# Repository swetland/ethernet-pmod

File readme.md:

# Ethernet PMOD v2

This PCB is a PMOD (FPGA development board peripheral module) for the
Microchip LAN8720A PHY, to enable 10/100M Ethernet connectivity.

It is configured to accept the necessary 50MHz clock from the FPGA, and
exchanges data using the [RMII standard](https://en.wikipedia.org/wiki/Media-independent_interface#RMII).  A secondary header provides access
to the MDIO/MDC lines to allow access to the management interface.

I have manufactured 10 of these using JLCPCB's PCB fabrication and assembly
service (manually soldering the two throw-hole components myself) and have
used this PMOD successfully with Litex / LiteETH / VexRiscv on a Muse Lab
iCE Sugar Pro FPGA board.

This project is licensed under the [CERN OHL P v2](CERN-OHL-P-v2.txt) Permissive Open Hardware License.

## Design Files and Resources

Original design files are here: [kicad/](kicad/)

Schematic in PDF format here: [export/ethernet-pmod-v2-schematic.pdf](export/ethernet-pmod-v2-schematic.pdf)

Gerbers and CSV files used for a successful JLCPCB order, under [export/jlcpcb/](export/jlcpcb/)

Documentation on the Microchip LAN8720A: https://www.microchip.com/en-us/product/LAN8720A

## Pictures

## PMOD Connector Layout

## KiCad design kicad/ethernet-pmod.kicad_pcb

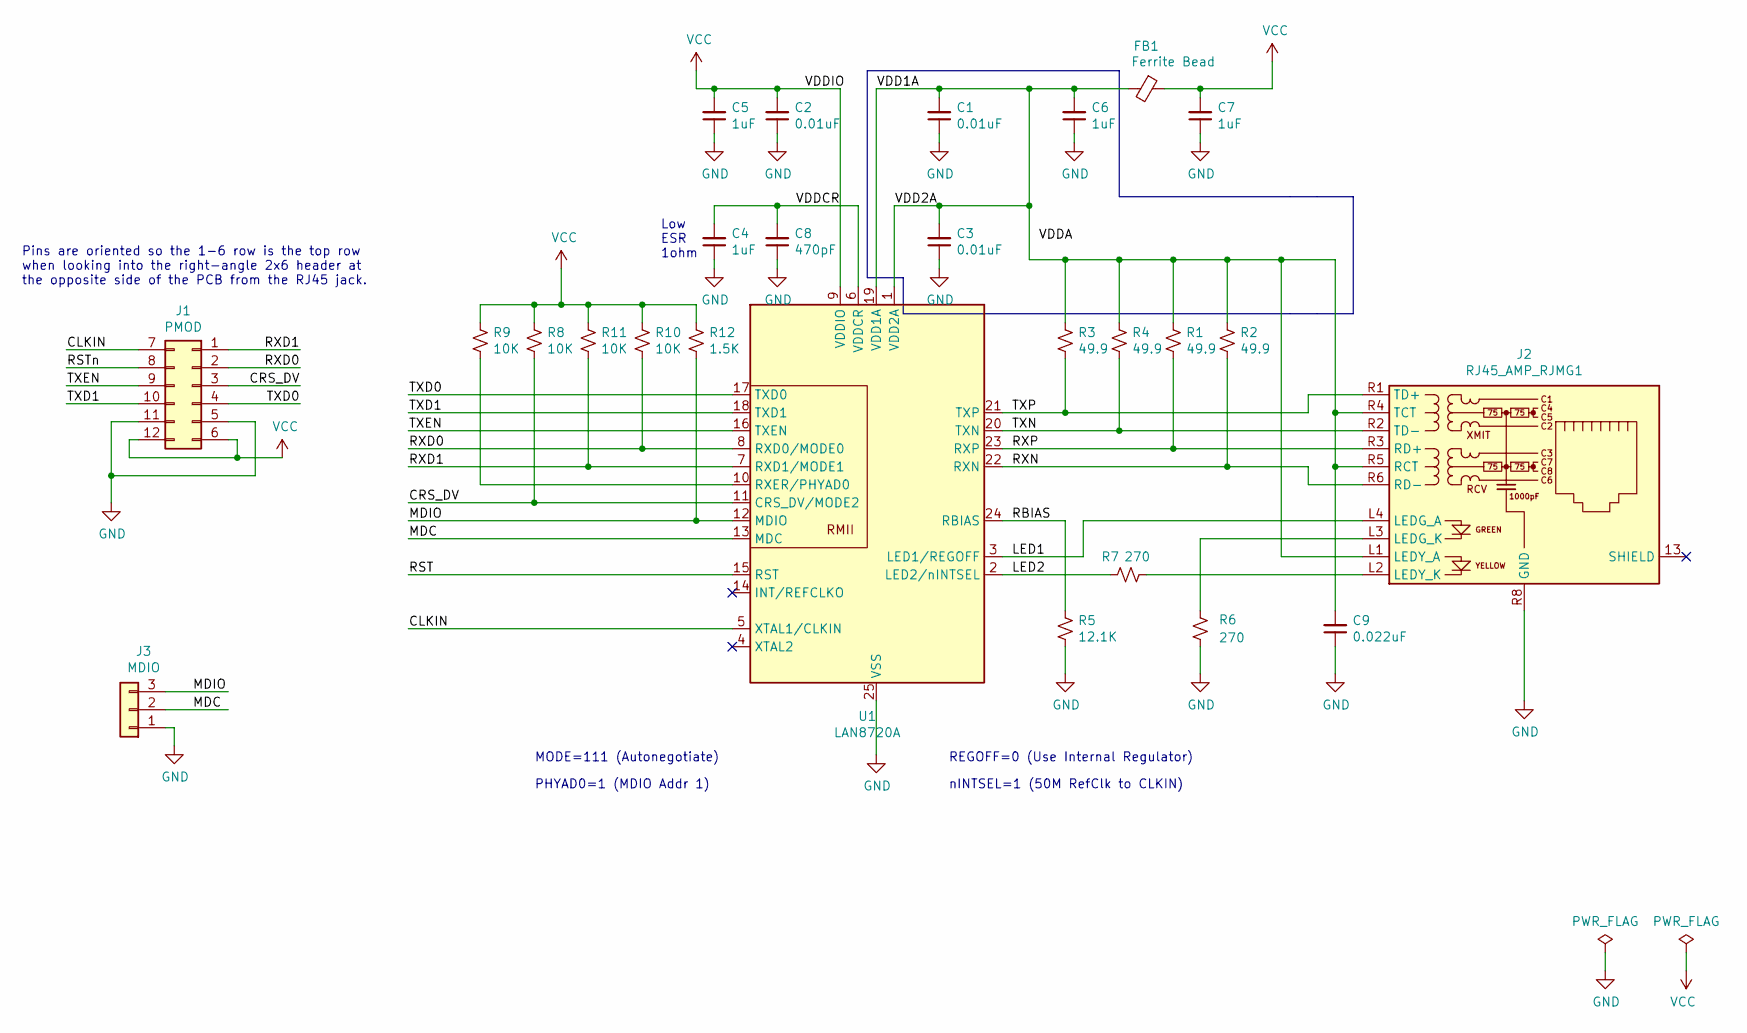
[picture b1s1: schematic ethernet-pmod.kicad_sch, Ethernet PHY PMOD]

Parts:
C1, C2, C3: 0.01uF; C_0402_1005Metric
C4, C5: 1uF; C_0402_1005Metric
C6, C7: 1uF; C_0603_1608Metric
C8: 470pF; C_0402_1005Metric
C9: 0.022uF; C_0402_1005Metric
FB1: Ferrite Bead; L_0805_2012Metric
J1: PMOD; PMOD_Peripheral_Conn_2x06_P2.54mm_Vertical
J2: RJ45_AMP_RJMG1; RJ45_Amphenol_RJMG1BD3B8K1ANR
J3: MDIO; PinSocket_1x03_P2.54mm_Vertical
R1, R2, R3, R4: 49.9; R_0402_1005Metric
R5: 12.1K; R_0402_1005Metric
R6, R7: 270; R_0402_1005Metric
R8, R9, R10, R11: 10K; R_0402_1005Metric
R12: 1.5K; R_0402_1005Metric
U1: LAN8720A; QFN-24-1EP_4x4mm_P0.5mm_EP2.6x2.6mm_ThermalVias

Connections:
/CLKIN: J1.7, U1.5 (XTAL1/CLKIN)
/CRS_DV: J1.3, R8.2, U1.11 (CRS_DV/MODE2)
/LED1: J2.L4 (LEDG_A), U1.3 (LED1/REGOFF)
/LED2: R7.2, U1.2 (LED2/nINTSEL)
/MDC: J3.2, U1.13 (MDC)
/MDIO: J3.3, R12.2, U1.12 (MDIO)
/RBIAS: R5.1, U1.24 (RBIAS)
/RST: U1.15 (RST)
/RSTn: J1.8
/RXD0: J1.2, R10.2, U1.8 (RXD0/MODE0)
/RXD1: J1.1, R11.2, U1.7 (RXD1/MODE1)
/RXN: J2.R6 (RD-), R2.2, U1.22 (RXN)
/RXP: J2.R3 (RD+), R1.2, U1.23 (RXP)
/TXD0: J1.4, U1.17 (TXD0)
/TXD1: J1.10, U1.18 (TXD1)
/TXEN: J1.9, U1.16 (TXEN)
/TXN: J2.R2 (TD-), R4.2, U1.20 (TXN)
/TXP: J2.R1 (TD+), R3.2, U1.21 (TXP)
/VDD1A: C1.2, C3.2, C6.2, C9.2, FB1.2, J2.L1 (LEDY_A), J2.R4 (TCT), J2.R5 (RCT), R1.1, R2.1, R3.1, R4.1, U1.1 (VDD2A), U1.19 (VDD1A)
/VDDCR: C4.2, C8.2, U1.6 (VDDCR)
GND: C1.1, C2.1, C3.1, C4.1, C5.1, C6.1, C7.1, C8.1, C9.1, J1.5, J1.11, J2.R8 (GND), J3.1, R5.2, R6.2, U1.25 (VSS)
unnamed: J2.L2 (LEDY_K), R7.1
unnamed: J2.L3 (LEDG_K), R6.1
unnamed: R9.2, U1.10 (RXER/PHYAD0)
VCC: C2.2, C5.2, C7.2, FB1.1, J1.6, J1.12, R8.1, R9.1, R10.1, R11.1, R12.1, U1.9 (VDDIO)

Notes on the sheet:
REGOFF=0 (Use Internal Regulator)
nINTSEL=1 (50M RefClk to CLKIN)
Low ESR 1ohm
PHYAD0=1 (MDIO Addr 1)
Pins are oriented so the 1-6 row is the top row when looking into the right-angle 2x6 header at the opposite side of the PCB from the RJ45 jack.
MODE=111 (Autonegotiate)

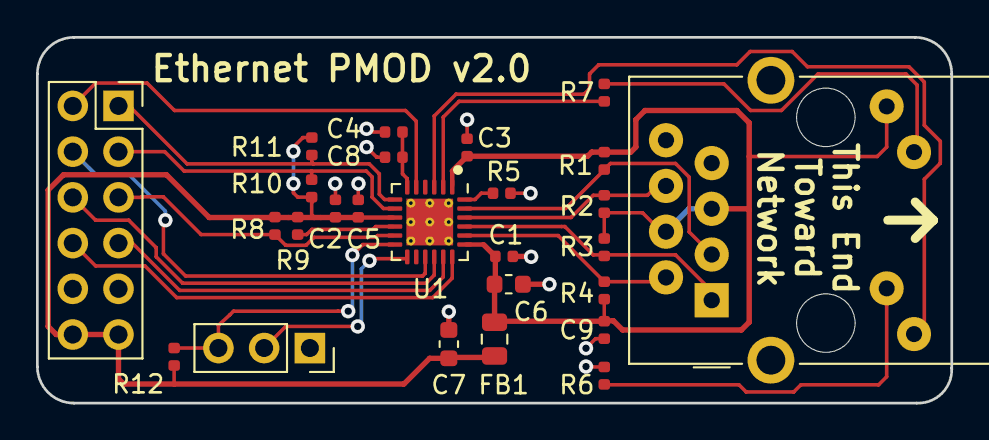
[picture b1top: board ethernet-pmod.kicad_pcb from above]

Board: 2 copper layers, 50.8 x 20.3 mm, 26 parts (0 on the bottom side), 23 nets.

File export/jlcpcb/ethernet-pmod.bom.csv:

Comment,Designator,Footprint,"JLCPCB Part #"
0.01uF,"C1,C2,C3",0402_C,C15195
1uF,"C4,C5",0402_C,C52923
1uF,"C6,C7",0603_C,C15849
470pF,C8,0402_C,C1537
0.022uF,C9,0402_C,C1532
FerriteBead,FB1,0805_I,C1015
49.9,"R1,R2,R3,R4",0402_R,C25120
12.1K,R5,0402_R,C25852
270,"R6,R7",0402_R,C25099
10K,"R8,R9,R10,R11",0402_R,C25744
1.5K,R12,0402_R,C25867
LAN8720A,U1,VQFN-24,C45223

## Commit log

2022-05-29 cleanup: improve PMOD header (J1) presentation in schematic
    - tidied up schematic
    - added commentary on pin orientation
    - renamed RST to RSTn for clarity
    - re-exported schematic to PDF
2022-05-29 docs: add picture of pmod connector pinout

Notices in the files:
kicad/ethernet-pmod.kicad_sch:
This source describes Open Hardware and is licensed under the CERN-OHL-P v2
Copyright 2022, Brian Swetland
